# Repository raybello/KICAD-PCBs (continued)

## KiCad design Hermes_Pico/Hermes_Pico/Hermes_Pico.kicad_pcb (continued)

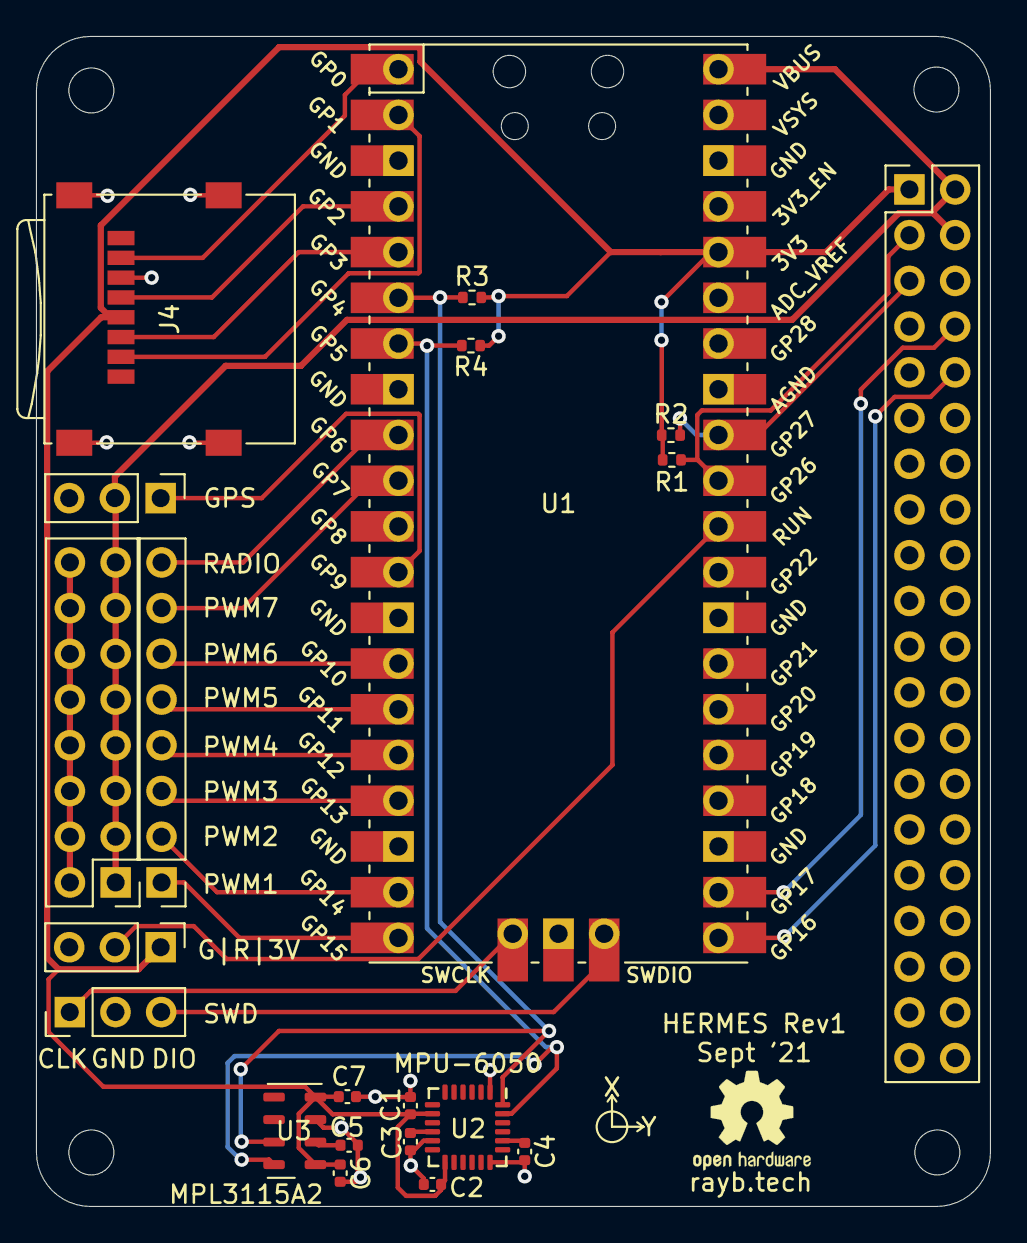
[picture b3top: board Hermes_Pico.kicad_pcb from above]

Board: 2 copper layers, 53.0 x 65.0 mm, 25 parts (0 on the bottom side), 28 nets.

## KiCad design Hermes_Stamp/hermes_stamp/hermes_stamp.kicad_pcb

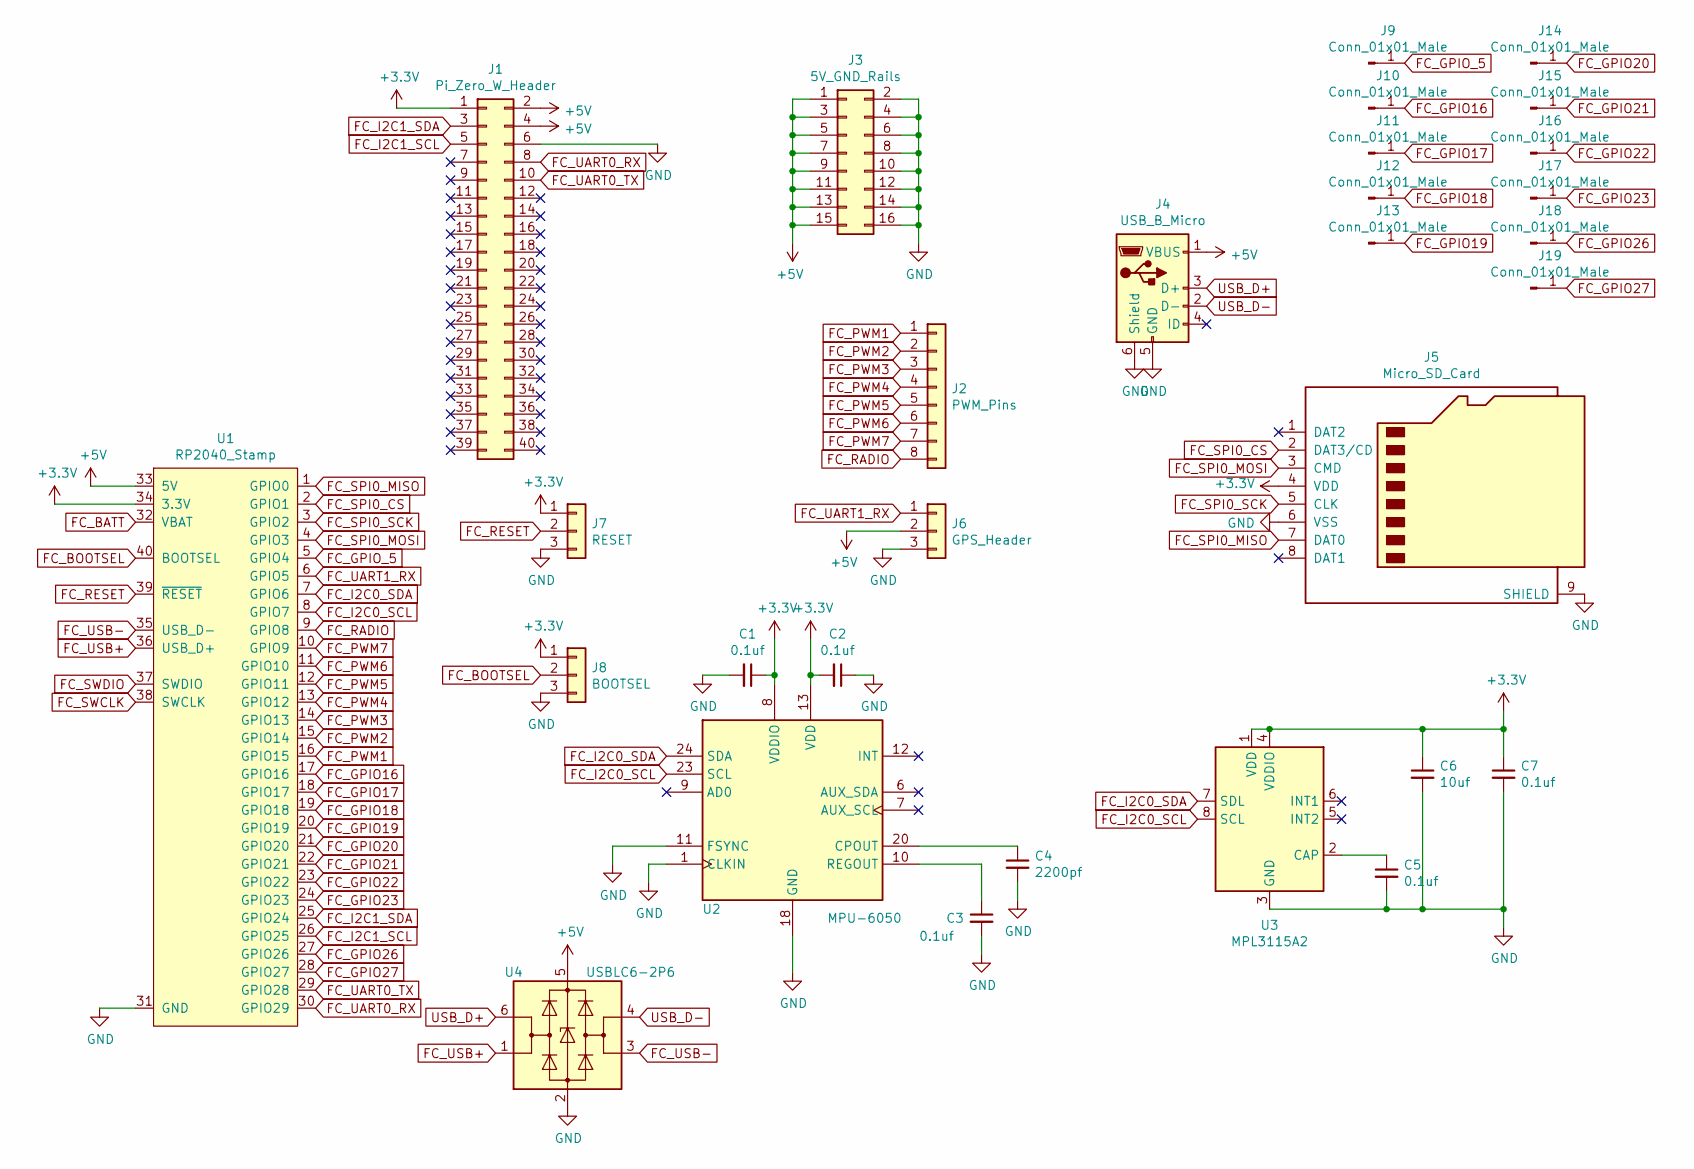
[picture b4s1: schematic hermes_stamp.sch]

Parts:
C1, C2, C3, C5, C7: 0.1uf; C_0402_1005Metric_Pad0.74x0.62mm_HandSolder
C4: 2200pf; C_0402_1005Metric_Pad0.74x0.62mm_HandSolder
C6: 10uf; C_0402_1005Metric_Pad0.74x0.62mm_HandSolder
J1: Pi_Zero_W_Header; PinHeader_2x20_P2.54mm_Vertical
J2: PWM_Pins; PinHeader_1x08_P2.54mm_Vertical
J3: 5V_GND_Rails; PinHeader_2x08_P2.54mm_Vertical
J4: USB_B_Micro; USB_Micro-B_Wuerth_629105150521
J5: Micro_SD_Card; microSD_HC_Wuerth_693072010801
J6: GPS_Header; PinHeader_1x03_P2.54mm_Vertical
J7: RESET; PinHeader_1x03_P2.54mm_Vertical
J8: BOOTSEL; PinHeader_1x03_P2.54mm_Vertical
J9, J10, J11, J12, J13, J14, J15, J16, J17, J18, J19: Conn_01x01_Male; SolderWire-0.1sqmm_1x01_D0.4mm_OD1mm
U1: RP2040_Stamp; RP2040_Stamp_SMD
U2: MPU-6050; InvenSense_QFN-24_4x4mm_P0.5mm
U3: MPL3115A2; NXP_LGA-8_3x5mm_P1.25mm_H1.1mm
U4: USBLC6-2P6; SOT-666

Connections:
+3V3: C1.1, C2.2, C6.1, C7.1, J1.1, J5.4 (VDD), J7.1, J8.1, U1.34 (3.3V), U2.8 (VDDIO), U2.13 (VDD), U3.1 (VDD), U3.4 (VDDIO)
+5V: J1.2, J1.4, J3.1, J3.3, J3.5, J3.7, J3.9, J3.11, J3.13, J3.15, J4.1 (VBUS), J6.2, U1.33 (5V), U4.5 (VBUS)
FC_BATT: U1.32 (VBAT)
FC_BOOTSEL: J8.2, U1.40 (BOOTSEL)
FC_GPIO16: J10.1, U1.17 (GPIO16)
FC_GPIO17: J11.1, U1.18 (GPIO17)
FC_GPIO18: J12.1, U1.19 (GPIO18)
FC_GPIO19: J13.1, U1.20 (GPIO19)
FC_GPIO20: J14.1, U1.21 (GPIO20)
FC_GPIO21: J15.1, U1.22 (GPIO21)
FC_GPIO22: J16.1, U1.23 (GPIO22)
FC_GPIO23: J17.1, U1.24 (GPIO23)
FC_GPIO26: J18.1, U1.27 (GPIO26)
FC_GPIO27: J19.1, U1.28 (GPIO27)
FC_GPIO_5: J9.1, U1.5 (GPIO4)
FC_I2C0_SCL: U1.8 (GPIO7), U2.23 (SCL), U3.8 (SCL)
FC_I2C0_SDA: U1.7 (GPIO6), U2.24 (SDA), U3.7 (SDL)
FC_I2C1_SCL: J1.5, U1.26 (GPIO25)
FC_I2C1_SDA: J1.3, U1.25 (GPIO24)
FC_PWM1: J2.1, U1.16 (GPIO15)
FC_PWM2: J2.2, U1.15 (GPIO14)
FC_PWM3: J2.3, U1.14 (GPIO13)
FC_PWM4: J2.4, U1.13 (GPIO12)
FC_PWM5: J2.5, U1.12 (GPIO11)
FC_PWM6: J2.6, U1.11 (GPIO10)
FC_PWM7: J2.7, U1.10 (GPIO9)
FC_RADIO: J2.8, U1.9 (GPIO8)
FC_RESET: J7.2, U1.39 (~RESET)
FC_SPI0_CS: J5.2 (DAT3/CD), U1.2 (GPIO1)
FC_SPI0_MISO: J5.7 (DAT0), U1.1 (GPIO0)
FC_SPI0_MOSI: J5.3 (CMD), U1.4 (GPIO3)
FC_SPI0_SCK: J5.5 (CLK), U1.3 (GPIO2)
FC_SWCLK: U1.38 (SWCLK)
FC_SWDIO: U1.37 (SWDIO)
FC_UART0_RX: J1.8, U1.30 (GPIO29)
FC_UART0_TX: J1.10, U1.29 (GPIO28)
FC_UART1_RX: J6.1, U1.6 (GPIO5)
FC_USB+: U1.36 (USB_D+), U4.1 (I/O1)
FC_USB-: U1.35 (USB_D-), U4.3 (I/O2)
GND: C1.2, C2.1, C3.2, C4.2, C5.2, C6.2, C7.2, J1.6, J3.2, J3.4, J3.6, J3.8, J3.10, J3.12, J3.14, J3.16, J4.5 (GND), J4.6 (Shield), J5.6 (VSS), J5.9 (SHIELD), J6.3, J7.3, J8.3, U1.31 (GND), U2.1 (CLKIN), U2.11 (FSYNC), U2.18 (GND), U3.3 (GND), U4.2 (GND)
unnamed: C3.1, U2.10 (REGOUT)
unnamed: C4.1, U2.20 (CPOUT)
unnamed: C5.1, U3.2 (CAP)
USB_D+: J4.3 (D+), U4.6 (I/O1)
USB_D-: J4.2 (D-), U4.4 (I/O2)

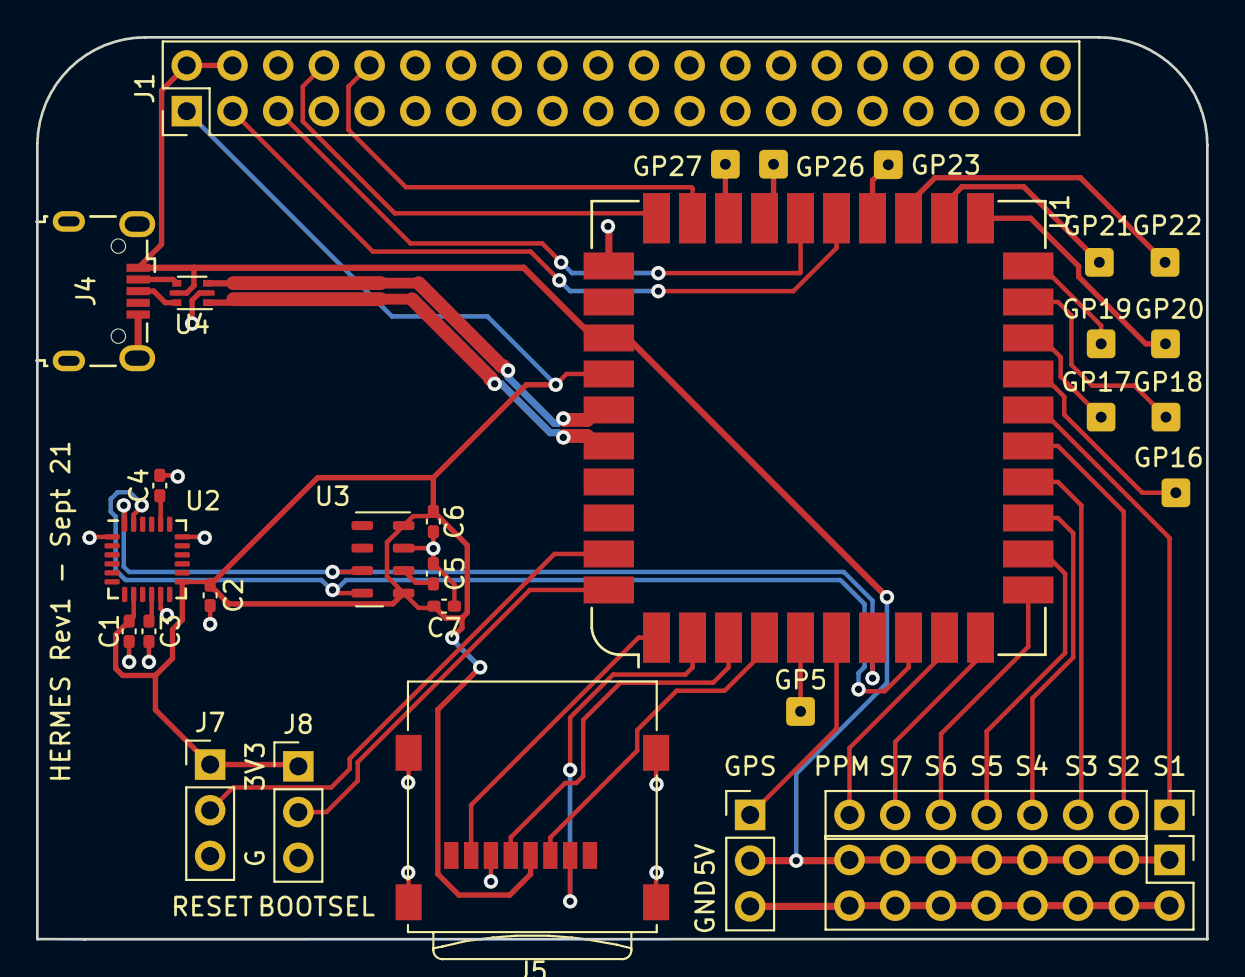
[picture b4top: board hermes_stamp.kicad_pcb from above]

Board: 2 copper layers, 65.0 x 50.1 mm, 30 parts (0 on the bottom side), 42 nets.

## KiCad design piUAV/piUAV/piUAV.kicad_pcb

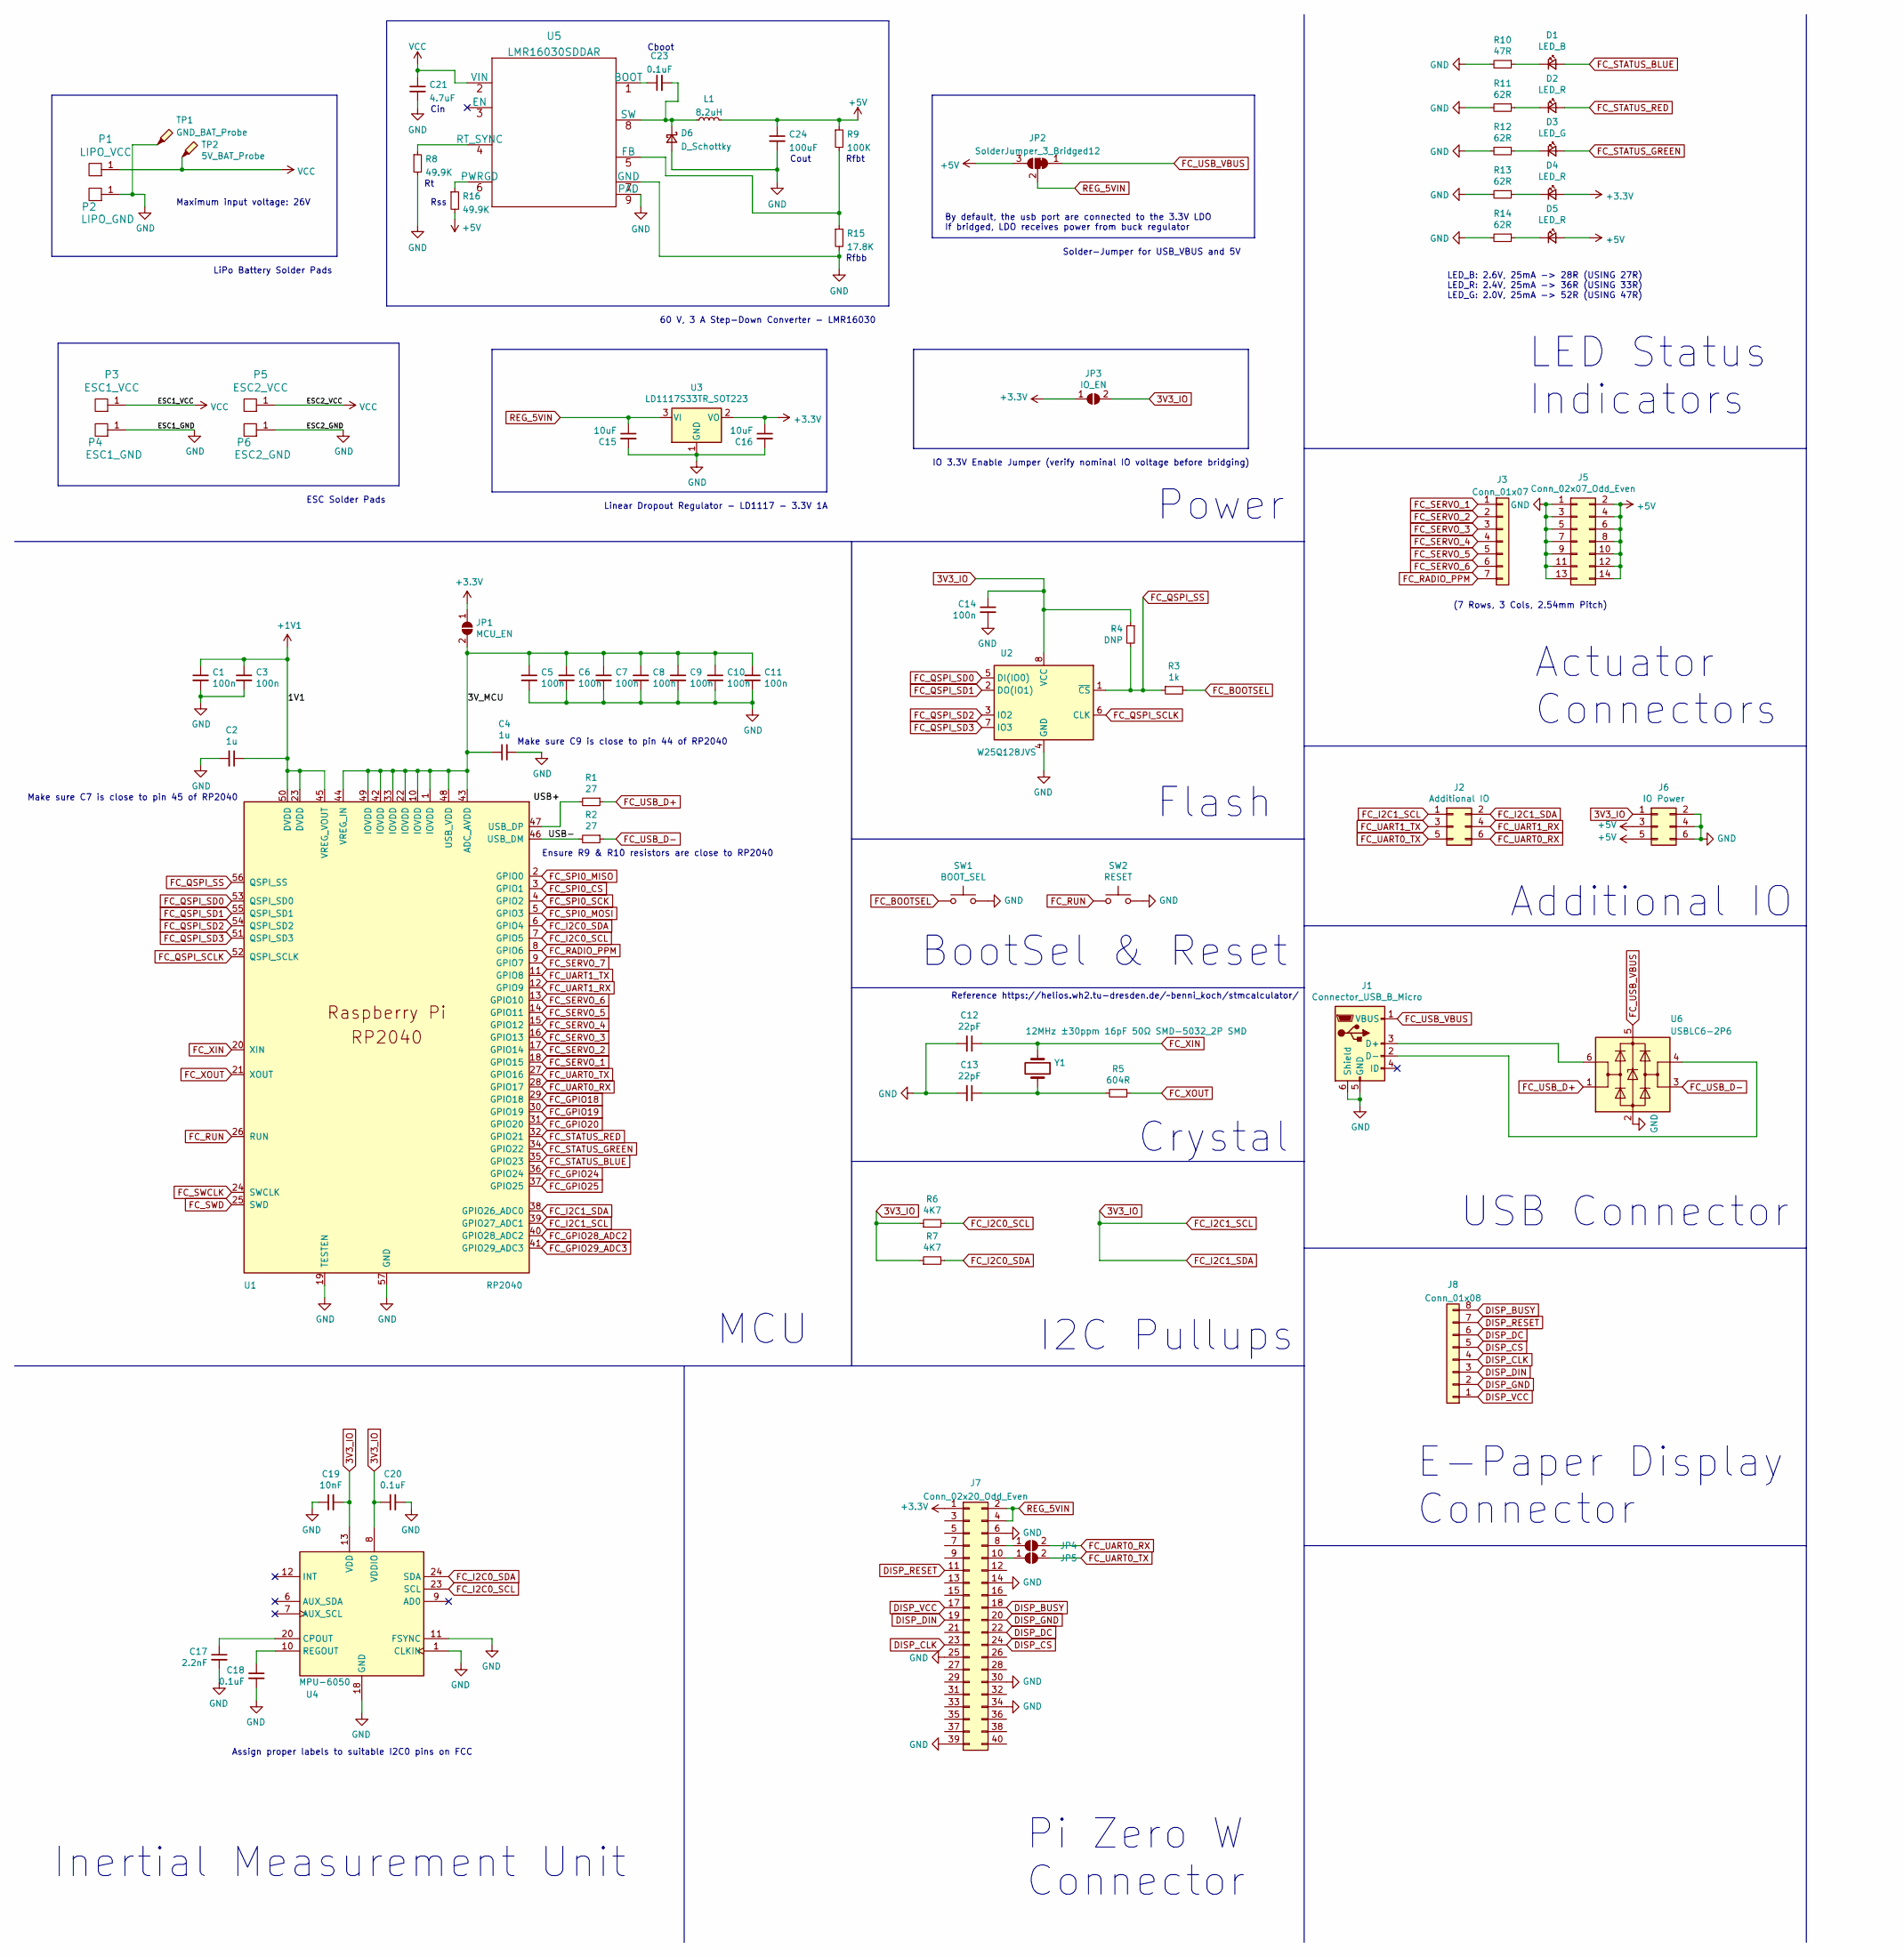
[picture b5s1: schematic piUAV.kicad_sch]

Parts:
C1, C3, C5, C6, C7, C8, C9, C10, C11, C14: 100n; C_0402_1005Metric_Pad0.74x0.62mm_HandSolder; LCSC C129131
C2, C4: 1u; C_0402_1005Metric_Pad0.74x0.62mm_HandSolder; LCSC C92755
C12, C13: 22pF; C_0402_1005Metric_Pad0.74x0.62mm_HandSolder; LCSC C342943
C15, C16: 10uF; C_0402_1005Metric_Pad0.74x0.62mm_HandSolder; LCSC C60133
C17: 2.2nF; C_0402_1005Metric_Pad0.74x0.62mm_HandSolder; LCSC C1531
C18, C20, C23: 0.1uF; C_0402_1005Metric_Pad0.74x0.62mm_HandSolder; LCSC C129131
C19: 10nF; C_0402_1005Metric_Pad0.74x0.62mm_HandSolder; LCSC C60133
C21: 4.7uF; C_0402_1005Metric_Pad0.74x0.62mm_HandSolder; LCSC C23733
C24: 100uF; C_1206_3216Metric; LCSC C15008
D1: LED_B; LED_0402_1005Metric_Pad0.77x0.64mm_HandSolder; LCSC C434447
D2, D4, D5: LED_R; LED_0402_1005Metric_Pad0.77x0.64mm_HandSolder; LCSC C136765
D3: LED_G; LED_0402_1005Metric_Pad0.77x0.64mm_HandSolder; LCSC C264408
D6: D_Schottky; D_SMA; LCSC C8678
J1: Connector_USB_B_Micro; USB_Micro-B_Amphenol_10118194_Horizontal; LCSC C132563
J2: Additional IO; PinHeader_2x03_P2.54mm_Vertical
J3: Conn_01x07; PinHeader_1x07_P2.54mm_Vertical
J5: Conn_02x07_Odd_Even; PinHeader_2x07_P2.54mm_Vertical
J6: IO Power; PinHeader_2x03_P2.54mm_Vertical
J7: Conn_02x20_Odd_Even; PinHeader_2x20_P2.54mm_Vertical
J8: Conn_01x08; PinHeader_1x08_P2.54mm_Vertical
JP1: MCU_EN; SolderJumper-2_P1.3mm_Open_RoundedPad1.0x1.5mm
JP2: SolderJumper_3_Bridged12; SolderJumper-3_P1.3mm_Bridged12_RoundedPad1.0x1.5mm_NumberL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
JP3: IO_EN; SolderJumper-2_P1.3mm_Open_RoundedPad1.0x1.5mm
JP4, JP5: SolderJumper_2_Open; SolderJumper-2_P1.3mm_Open_RoundedPad1.0x1.5mm
L1: 8.2uH; L_7.3x7.3_H3.5; LCSC C334083
P1: LIPO_VCC; TestPoint_Pad_2.0x2.0mm
P2: LIPO_GND; TestPoint_Pad_D2.0mm
P3: ESC1_VCC; TestPoint_Pad_2.0x2.0mm
P4: ESC1_GND; TestPoint_Pad_D2.0mm
P5: ESC2_VCC; TestPoint_Pad_2.0x2.0mm
P6: ESC2_GND; TestPoint_Pad_D2.0mm
R1, R2: 27; R_0402_1005Metric_Pad0.72x0.64mm_HandSolder; LCSC C413051
R3: 1k; R_0402_1005Metric_Pad0.72x0.64mm_HandSolder; LCSC C226166
R4: DNP; R_0402_1005Metric_Pad0.72x0.64mm_HandSolder
R5: 604R; R_0402_1005Metric_Pad0.72x0.64mm_HandSolder; LCSC C273693
R6, R7: 4K7; R_0402_1005Metric_Pad0.72x0.64mm_HandSolder; LCSC C304616
R8, R16: 49.9K; R_0402_1005Metric_Pad0.72x0.64mm_HandSolder; LCSC C25897
R9: 100K; R_0402_1005Metric_Pad0.72x0.64mm_HandSolder; LCSC C25741
R10: 47R; R_0402_1005Metric_Pad0.72x0.64mm_HandSolder; LCSC C25118
R11, R12, R13, R14: 62R; R_0402_1005Metric_Pad0.72x0.64mm_HandSolder; LCSC C227405
R15: 17.8K; R_0402_1005Metric_Pad0.72x0.64mm_HandSolder; LCSC C129766
SW1: BOOT_SEL; SW_SPST_PTS810; LCSC C92589
SW2: RESET; SW_SPST_PTS810; LCSC C92589
TP1: GND_BAT_Probe; TestPoint_Pad_D1.0mm
TP2: 5V_BAT_Probe; TestPoint_Pad_D1.0mm
U1: RP2040; RP2040-QFN-56; LCSC C2040
U2: W25Q128JVS; SOIC-8_5.23x5.23mm_P1.27mm; LCSC C97521
U3: LD1117S33TR_SOT223; SOT-223-3_TabPin2; LCSC C347229
U4: MPU-6050; InvenSense_QFN-24_4x4mm_P0.5mm; LCSC C24112
U5: LMR16030SDDAR; LCSC C136648
U6: USBLC6-2P6; SOT-666; LCSC C15999
Y1: 12MHz ±30ppm 16pF 50Ω SMD-5032_2P SMD; Crystal_SMD_TXC_7A-2Pin_5x3.2mm; LCSC C90884

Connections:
3V3_IO: C14.1, C19.2, C20.1, J2.1, J2.2, J6.1, JP3.2 (B), R4.1, R6.1, R7.1, U1.38 (GPIO26_ADC0), U1.39 (GPIO27_ADC1), U2.8 (VCC), U4.8 (VDDIO), U4.13 (VDD)
+1V1: C1.1, C2.1, C3.1, U1.23 (DVDD), U1.45 (VREG_VOUT), U1.50 (DVDD)
+3V3: C16.1, D4.2 (A), J7.1, JP1.1 (A), JP3.1 (A), U3.2 (VO)
+5V: C24.1, D5.2 (A), J5.2, J5.4, J5.6, J5.8, J5.10, J5.12, J5.14, J6.3, J6.5, JP2.3 (B), L1.2, R9.1, R16.2
/3V_MCU: C4.1, C5.1, C6.1, C7.1, C8.1, C9.1, C10.1, C11.1, JP1.2 (B), U1.1 (IOVDD), U1.10 (IOVDD), U1.22 (IOVDD), U1.33 (IOVDD), U1.42 (IOVDD), U1.43 (ADC_AVDD), U1.44 (VREG_IN), U1.48 (USB_VDD), U1.49 (IOVDD)
/USB+: R1.2, U1.47 (USB_DP)
/USB-: R2.2, U1.46 (USB_DM)
DISP_BUSY: J7.18, J8.8
DISP_CLK: J7.23, J8.4
DISP_CS: J7.24, J8.5
DISP_DC: J7.22, J8.6
DISP_DIN: J7.19, J8.3
DISP_GND: J7.20, J8.2
DISP_RESET: J7.11, J8.7
DISP_VCC: J7.17, J8.1
FC_BOOTSEL: R3.2, SW1.1
FC_GPIO18: U1.29 (GPIO18)
FC_GPIO19: U1.30 (GPIO19)
FC_GPIO20: U1.31 (GPIO20)
FC_GPIO24: U1.36 (GPIO24)
FC_GPIO25: U1.37 (GPIO25)
FC_GPIO28_ADC2: U1.40 (GPIO28_ADC2)
FC_GPIO29_ADC3: U1.41 (GPIO29_ADC3)
FC_I2C0_SCL: R6.2, U1.7 (GPIO5), U4.23 (SCL)
FC_I2C0_SDA: R7.2, U1.6 (GPIO4), U4.24 (SDA)
FC_QSPI_SCLK: U1.52 (QSPI_SCLK), U2.6 (CLK)
FC_QSPI_SD0: U1.53 (QSPI_SD0), U2.5 (DI(IO0))
FC_QSPI_SD1: U1.55 (QSPI_SD1), U2.2 (DO(IO1))
FC_QSPI_SD2: U1.54 (QSPI_SD2), U2.3 (IO2)
FC_QSPI_SD3: U1.51 (QSPI_SD3), U2.7 (IO3)
FC_QSPI_SS: R3.1, R4.2, U1.56 (QSPI_SS), U2.1 (~CS)
FC_RADIO_PPM: J3.7, U1.8 (GPIO6)
FC_RUN: SW2.1, U1.26 (RUN)
FC_SERVO_1: J3.1, U1.18 (GPIO15)
FC_SERVO_2: J3.2, U1.17 (GPIO14)
FC_SERVO_3: J3.3, U1.16 (GPIO13)
FC_SERVO_4: J3.4, U1.15 (GPIO12)
FC_SERVO_5: J3.5, U1.14 (GPIO11)
FC_SERVO_6: J3.6, U1.13 (GPIO10)
FC_SERVO_7: U1.9 (GPIO7)
FC_SPI0_CS: U1.3 (GPIO1)
FC_SPI0_MISO: U1.2 (GPIO0)
FC_SPI0_MOSI: U1.5 (GPIO3)
FC_SPI0_SCK: U1.4 (GPIO2)
FC_STATUS_BLUE: D1.2 (A), U1.35 (GPIO23)
FC_STATUS_GREEN: D3.2 (A), U1.34 (GPIO22)
FC_STATUS_RED: D2.2 (A), U1.32 (GPIO21)
FC_SWCLK: U1.24 (SWCLK)
FC_SWD: U1.25 (SWD)
FC_UART0_RX: J2.6, JP4.2 (B), U1.28 (GPIO17)
FC_UART0_TX: J2.5, JP5.2 (B), U1.27 (GPIO16)
FC_UART1_RX: J2.4, U1.12 (GPIO9)
FC_UART1_TX: J2.3, U1.11 (GPIO8)
FC_USB_D+: R1.1, U6.1 (I/O1)
FC_USB_D-: R2.1, U6.3 (I/O2)
FC_USB_VBUS: J1.1 (VBUS), JP2.1 (A), U6.5 (VBUS)
FC_XIN: C12.1, U1.20 (XIN), Y1.1
FC_XOUT: R5.1, U1.21 (XOUT)
GND: C1.2, C2.2, C3.2, C4.2, C5.2, C6.2, C7.2, C8.2, C9.2, C10.2, C11.2, C12.2, C13.2, C14.2, C15.2, C16.2, C17.2, C18.2, C19.1, C20.2, C21.2, C24.2, D6.2 (A), J1.5 (GND), J1.6 (Shield), J5.1, J5.3, J5.5, J5.7, J5.9, J5.11, J5.13, J6.2, J6.4, J6.6, J7.6, J7.14, J7.25, J7.30, J7.34, J7.39, P2.1 (PAD), P4.1 (PAD), P6.1 (PAD), R8.2, R10.2, R11.2, R12.2, R13.2, R14.2, R15.2, SW1.2, SW2.2, TP1.1, U1.19 (TESTEN), U1.57 (GND), U2.4 (GND), U3.1 (GND), U4.1 (CLKIN), U4.11 (FSYNC), U4.18 (GND), U5.7 (GND), U5.9 (PAD), U6.2 (GND)
unnamed: C13.1, R5.2, Y1.2
unnamed: C17.1, U4.20 (CPOUT)
unnamed: C18.1, U4.10 (REGOUT)
unnamed: C23.1, U5.1 (BOOT)
unnamed: C23.2, D6.1 (K), L1.1, U5.8 (SW)
unnamed: D1.1 (K), R10.1
unnamed: D2.1 (K), R11.1
unnamed: D3.1 (K), R12.1
unnamed: D4.1 (K), R13.1
unnamed: D5.1 (K), R14.1
unnamed: J1.2 (D-), U6.4 (I/O2)
unnamed: J1.3 (D+), U6.6 (I/O1)
unnamed: J7.8, JP4.1 (A)
unnamed: J7.10, JP5.1 (A)
unnamed: R8.1, U5.4 (RT_SYNC)
unnamed: R9.2, R15.1, U5.5 (FB)
unnamed: R16.1, U5.6 (PWRGD)
REG_5VIN: C15.1, J7.2, J7.4, JP2.2 (C), U3.3 (VI)
VCC: C21.1, P1.1 (PAD), P3.1 (PAD), P5.1 (PAD), TP2.1, U5.2 (VIN)

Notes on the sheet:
Rfbt
(7 Rows, 3 Cols, 2.54mm Pitch)
Flash
Pi Zero W Connector
Rfbb
Cboot
MCU
Additional IO
Make sure C7 is close to pin 45 of RP2040
I2C Pullups
Linear Dropout Regulator - LD1117 - 3.3V 1A
By default, the usb port are connected to the 3.3V LDO If bridged, LDO receives power from buck regulator
LED_B: 2.6V, 25mA -> 28R (USING 27R) LED_R: 2.4V, 25mA -> 36R (USING 33R) LED_G: 2.0V, 25mA -> 52R (USING 47R)
Reference https://helios.wh2.tu-dresden.de/~benni_koch/stmcalculator/
Cin
Ensure R9 & R10 resistors are close to RP2040
Cout
USB Connector
Actuator Connectors
ESC Solder Pads
Assign proper labels to suitable I2C0 pins on FCC
Power
60 V, 3 A Step-Down Converter - LMR16030
E-Paper Display Connector
IO 3.3V Enable Jumper (verify nominal IO voltage before bridging)
Rss
BootSel & Reset
LiPo Battery Solder Pads
Inertial Measurement Unit
Crystal
Maximum input voltage: 26V
Solder-Jumper for USB_VBUS and 5V
LED Status Indicators
Make sure C9 is close to pin 44 of RP2040

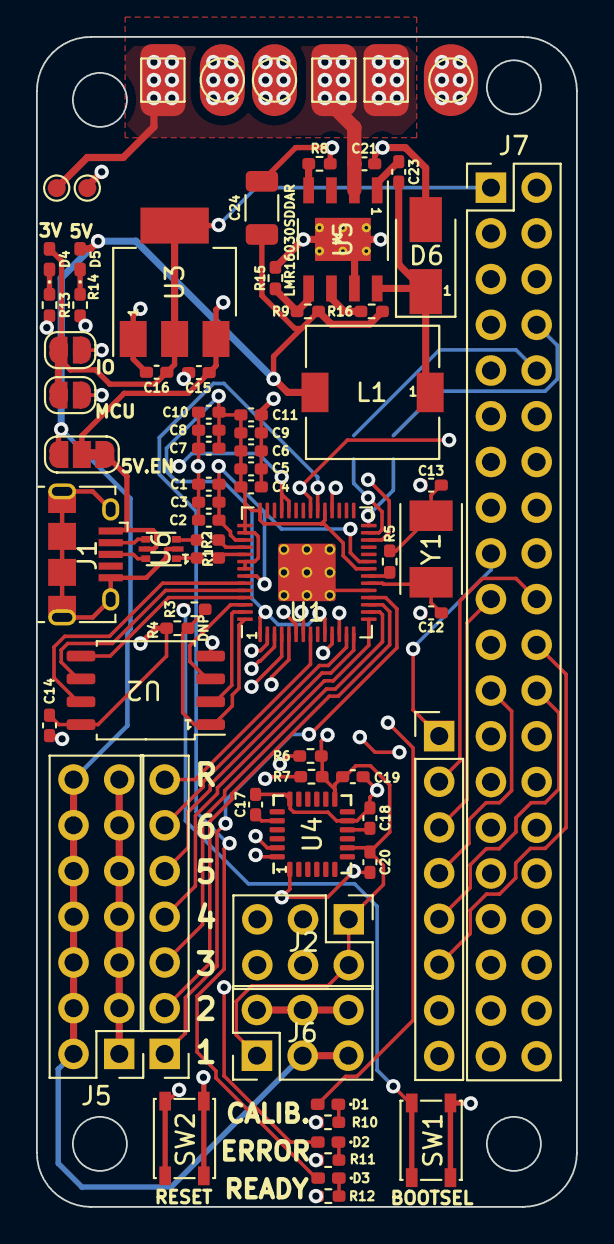
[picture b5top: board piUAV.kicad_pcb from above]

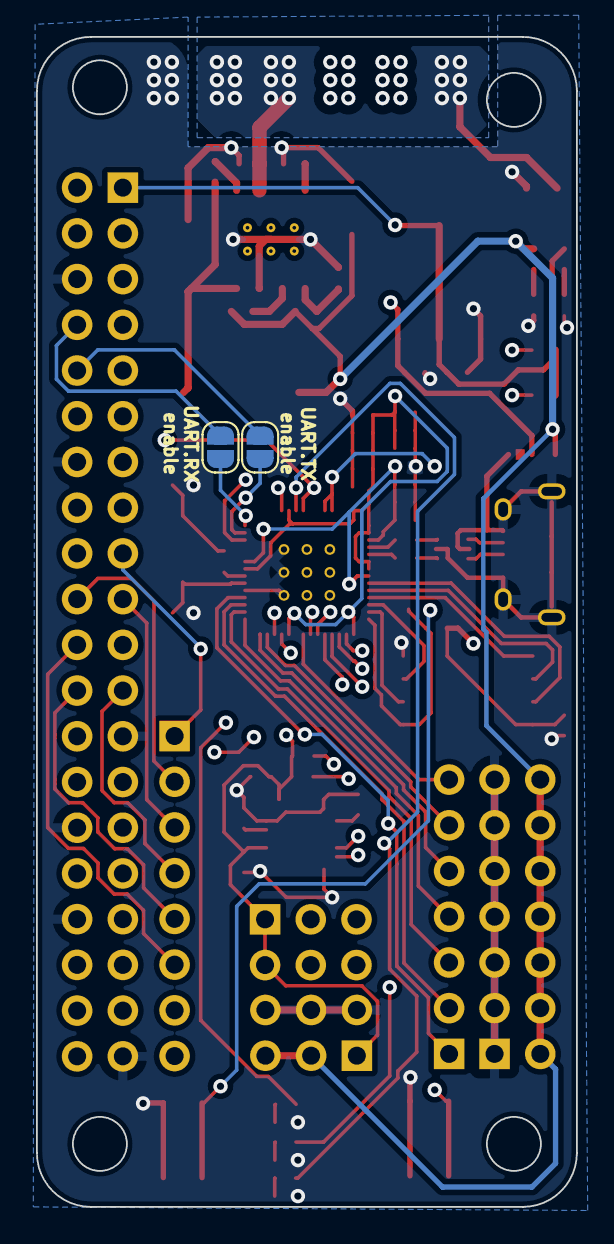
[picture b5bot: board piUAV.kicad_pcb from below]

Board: 4 copper layers, 30.0 x 65.0 mm, 75 parts (2 on the bottom side), 64 nets.
